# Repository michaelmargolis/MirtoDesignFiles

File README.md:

# MirtoDesignFiles

Design files for Mirto Robots

Mirto_Hubee robot has a Teensy3 controller driving HUBee wheels 

Mirto_Hotec has a teensy3 controller driving Hotec motors

Mirto_MyRio uses National Instruments myRIO to control Hotec Motors.

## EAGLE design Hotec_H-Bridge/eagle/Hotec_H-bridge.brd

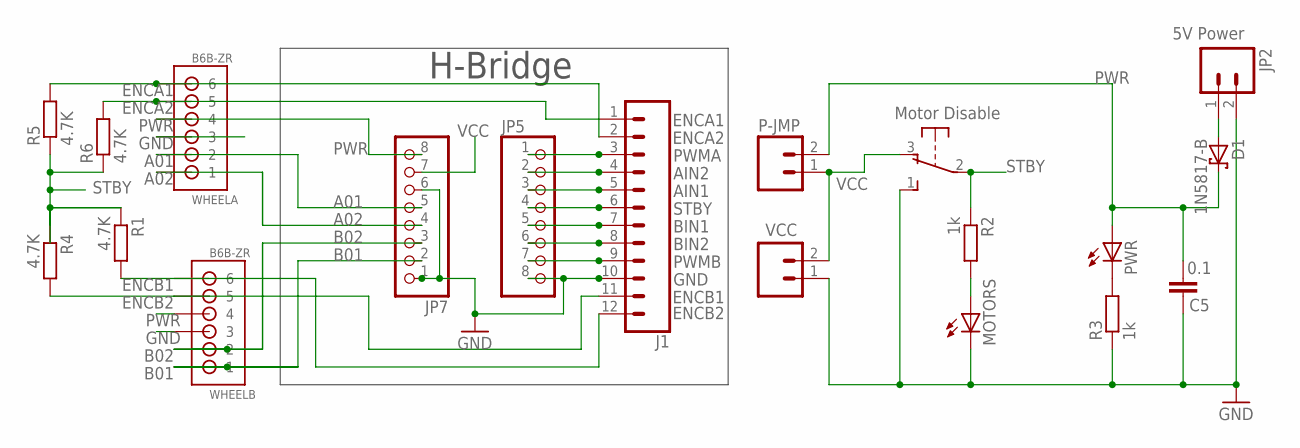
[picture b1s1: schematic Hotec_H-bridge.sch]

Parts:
C5: 0.1; CAP-PTH-SMALLEZ
D1: 1N5817-B; DO41-7.6
J1: CONN_12; 1X12
JP2: M023.5MM; SCREWTERMINAL-3.5MM-2
JP5, JP7: PINHD-1X8CLEANBIG; 1X08-CLEANBIG
MOTORS: LED3MM
P-JMP: M02PTH; 1X02
PWR: LED3MM
R1, R4, R5, R6: 4.7K; 0204/7
R2, R3: 1k; 0204/7
SW1: OS102011MA1Q
VCC: M02PTH; 1X02
WHEELA: B6B-ZR
WHEELB: B6B-ZR

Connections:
A01: JP7.5, WHEELA.2
A02: JP7.4, WHEELA.1
AIN1: J1.5, JP5.3
AIN2: J1.4, JP5.2
B01: JP7.2, WHEELB.1
B02: JP7.3, WHEELB.2
BIN1: J1.7, JP5.5
BIN2: J1.8, JP5.6
ENCA1: J1.2, R5.2, WHEELA.6
ENCA2: J1.1, R6.2, WHEELA.5
ENCB1: J1.12, R1.2, WHEELB.6
ENCB2: J1.11, R4.2, WHEELB.5
GND: C5.1, J1.10, JP2.2, JP5.8, JP7.1, JP7.6, MOTORS.K (C), R3.1, SW1.1 (S), VCC.1, WHEELA.3, WHEELB.3
unnamed: PWR.K (C), R3.2
unnamed: MOTORS.A, R2.2
unnamed: D1.A, JP2.1
PWMA: J1.3, JP5.1
PWMB: J1.9, JP5.7
PWR: C5.2, D1.C, JP7.8, P-JMP.2, PWR.A, WHEELA.4, WHEELB.4
STBY: J1.6, JP5.4, R1.1, R2.1, R4.1, R5.1, R6.1, SW1.2
VCC: JP7.7, P-JMP.1, SW1.3 (O), VCC.2

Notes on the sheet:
Motor Disable
5V Power
H-Bridge

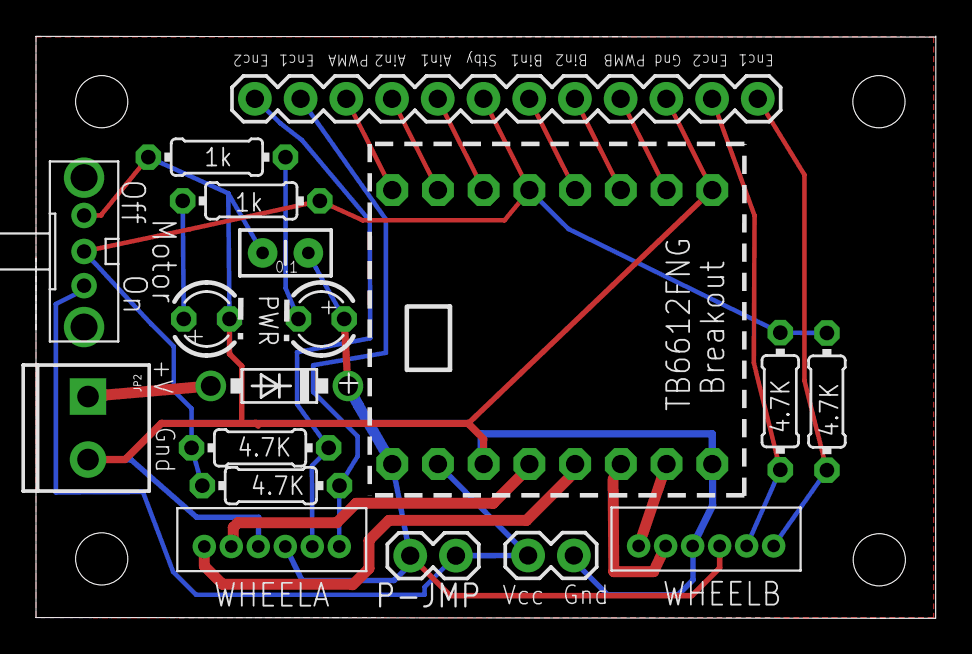
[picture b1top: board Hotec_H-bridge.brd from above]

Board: 2 copper layers, 50.0 x 32.4 mm, 19 parts (0 on the bottom side), 21 nets.

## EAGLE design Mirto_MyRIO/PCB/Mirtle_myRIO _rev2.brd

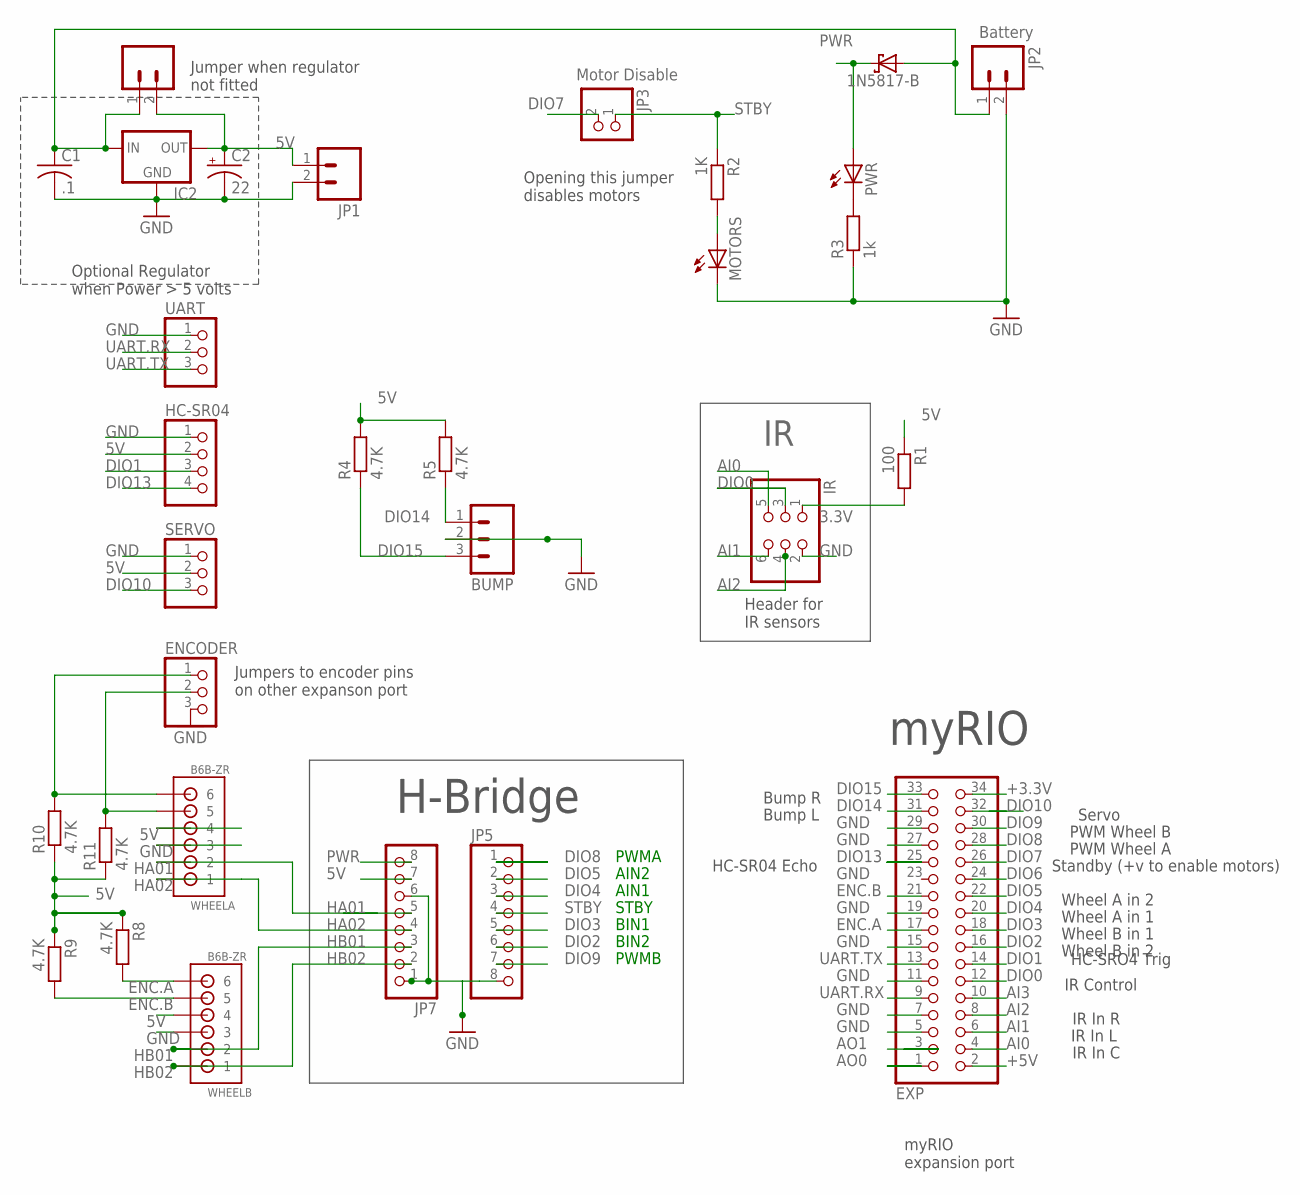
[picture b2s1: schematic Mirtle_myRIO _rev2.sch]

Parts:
5VJMPR: M02PTH; 1X02
BUMP: M03SCREW; SCREWTERMINAL-3.5MM-3
C1: .1; C025-024X044
C2: 22; E2-5
D1: 1N5817-B; DO41-7.6
ENCODER: PINHD-1X3/90; 1X03/90
EXP: PINHD-2X17/90; 2X17/90
HC-SR04: PINHD-1X4/90; 1X04/90
IC2: 78MXXS
IR: PINHD-2X3; 2X03
JP1, JP2: M023.5MM; SCREWTERMINAL-3.5MM-2
JP3: PINHD-1X2/90; 1X02/90
JP5, JP7: PINHD-1X8CLEANBIG; 1X08-CLEANBIG
MOTORS: LED3MM
PWR: LED3MM
R1: 100; 0204/7
R2: 1K; 0204/7
R3: 1k; 0204/7
R4, R5, R8, R9, R10, R11: 4.7K; 0204/7
SERVO: PINHD-1X3/90; 1X03/90
UART: PINHD-1X3/90; 1X03/90
WHEELA: B6B-ZR
WHEELB: B6B-ZR

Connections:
3.3V: IR.1, R1.2
5V: 5VJMPR.2, C2.+, HC-SR04.2, IC2.OUT, JP1.1, JP7.7, R1.1, R4.2, R5.2, R8.1, R9.1, R10.1, R11.1, SERVO.2, WHEELA.4, WHEELB.4
+3.3V: EXP.34
+5V: EXP.2
AI0: EXP.4, IR.5
AI1: EXP.6, IR.6
AI2: EXP.8, IR.4
AI3: EXP.10
AO0: EXP.1
AO1: EXP.3
BAT+V: 5VJMPR.1, C1.1, D1.A, IC2.IN, JP2.1
D31: ENCODER.1, R10.2, WHEELA.6
DIO0: EXP.12, IR.3
DIO1: EXP.14, HC-SR04.3
DIO2: EXP.16, JP5.6
DIO3: EXP.18, JP5.5
DIO4: EXP.20, JP5.3
DIO5: EXP.22, JP5.2
DIO6: EXP.24
DIO7: EXP.26, JP3.2
DIO8: EXP.28, JP5.1
DIO9: EXP.30, JP5.7
DIO10: EXP.32, SERVO.3
DIO13: EXP.25, HC-SR04.4
DIO14: BUMP.1, EXP.31, R5.1
DIO15: BUMP.3, EXP.33, R4.1
ENC.A: EXP.17, R8.2, WHEELB.6
ENC.B: EXP.21, R9.2, WHEELB.5
GND: BUMP.2, C1.2, C2.-, ENCODER.3, EXP.5, EXP.7, EXP.11, EXP.15, EXP.19, EXP.27, EXP.29, HC-SR04.1, IC2.GND, IR.2, JP1.2, JP2.2, JP5.8, JP7.1, JP7.6, MOTORS.K (C), R3.1, SERVO.1, UART.1, WHEELA.3, WHEELB.3
HA01: JP7.5, WHEELA.2
HA02: JP7.4, WHEELA.1
HB01: JP7.3, WHEELB.2
HB02: JP7.2, WHEELB.1
unnamed: PWR.K (C), R3.2
unnamed: ENCODER.2, R11.2, WHEELA.5
unnamed: MOTORS.A, R2.2
PWR: D1.C, JP7.8, PWR.A
STBY: JP3.1, JP5.4, R2.1
UART.RX: EXP.9, UART.2
UART.TX: EXP.13, UART.3

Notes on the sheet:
Motor Disable
Battery
Header for IR sensors
H-Bridge
myRIO
Jumpers to encoder pins on other expanson port
STBY
myRIO expansion port
AIN1
AIN2
PWMA
BIN1
BIN2
PWMB
IR In L
IR Control
Bump L
IR In C
IR In R
Bump R
HC-SR04 Echo
PWM Wheel A
PWM Wheel B
Wheel B in 1
Wheel B in 2
Wheel A in 1
Wheel A in 2
Servo
HC-SRO4 Trig
Standby (+v to enable motors)
Optional Regulator when Power > 5 volts
Jumper when regulator not fitted
Opening this jumper disables motors

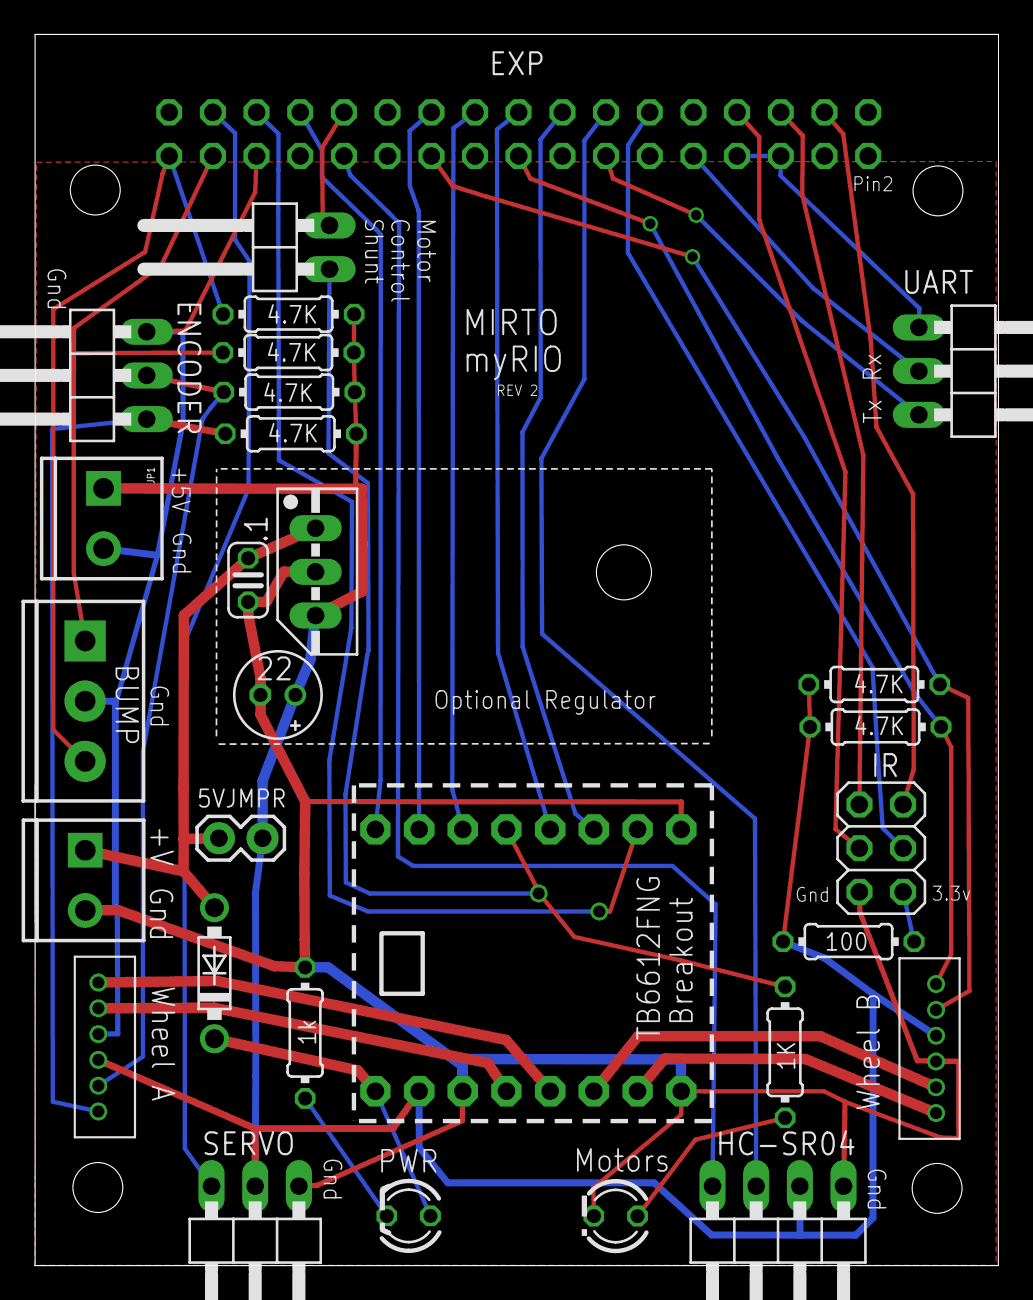
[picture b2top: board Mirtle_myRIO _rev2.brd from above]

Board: 4 copper layers, 56.1 x 71.6 mm, 30 parts (1 on the bottom side), 34 nets.

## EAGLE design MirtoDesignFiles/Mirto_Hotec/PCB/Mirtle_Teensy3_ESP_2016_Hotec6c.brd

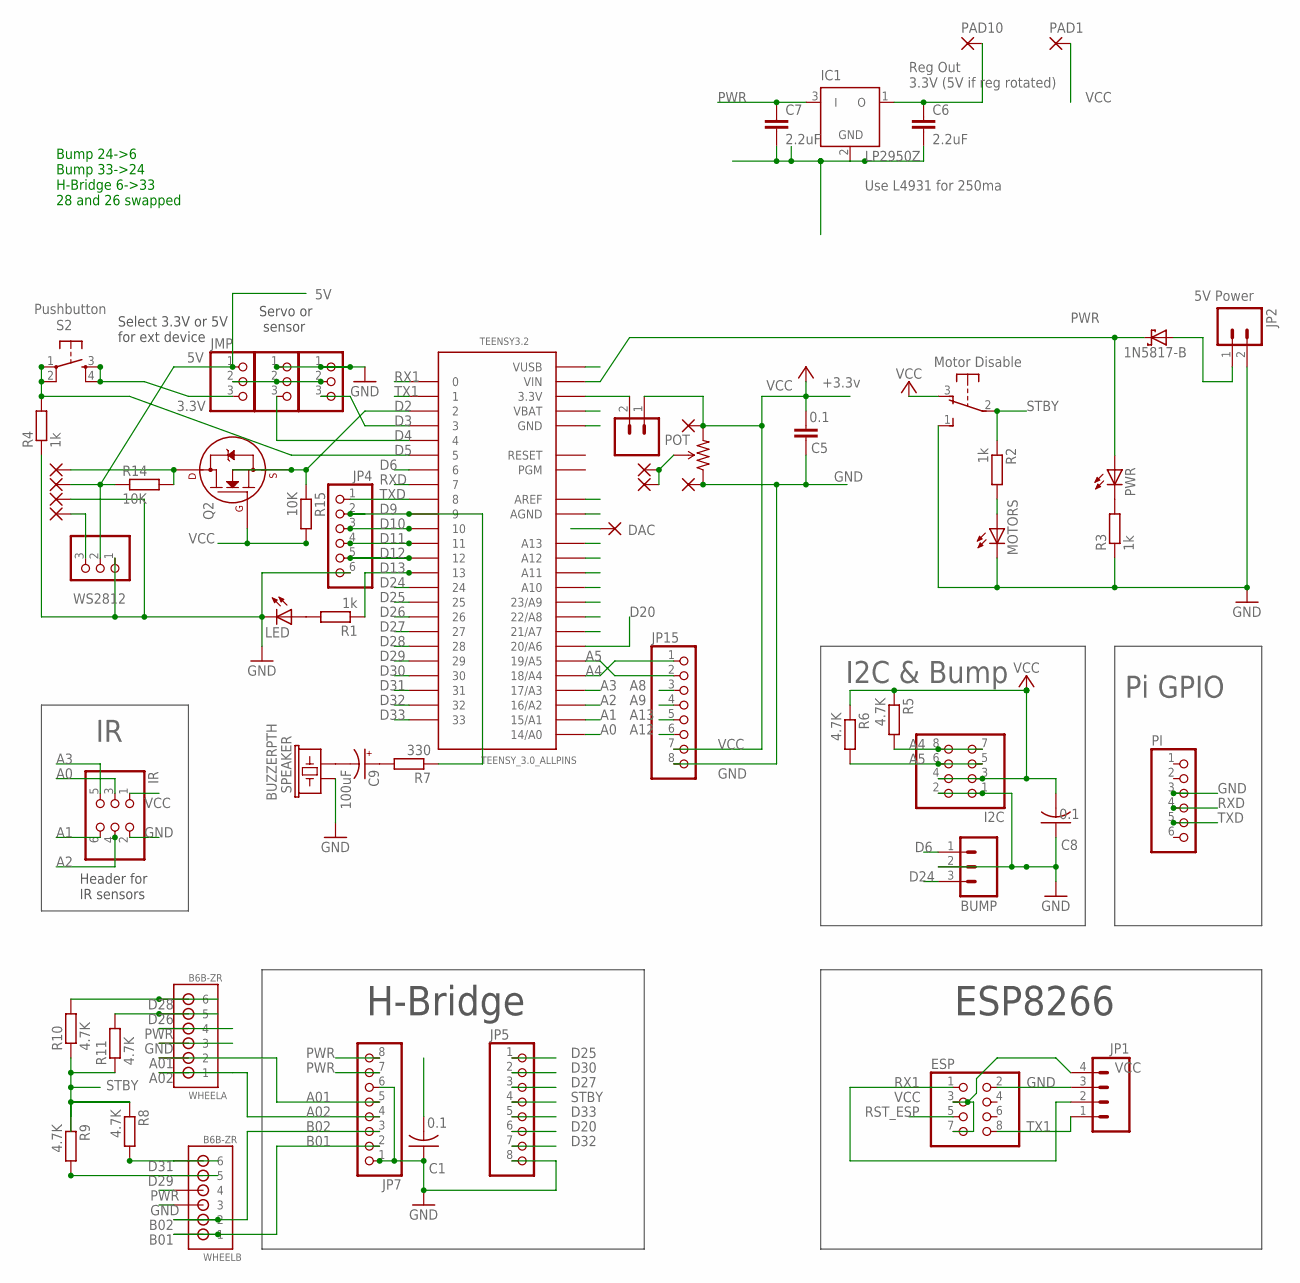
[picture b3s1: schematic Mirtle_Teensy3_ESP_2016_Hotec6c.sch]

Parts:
3V3: M02PTH; 1X02
BUMP: M03SCREW; SCREWTERMINAL-3.5MM-3
C1, C8: 0.1; C025-024X044
C5: 0.1; CAP-PTH-SMALLEZ
C6, C7: 2.2uF; C050-024X044
C9: 100uF; E2,5-5
D1: 1N5817-B; DO41-7.6
DAC: 1,6/0,8
ESP: PINHD-2X4; 2X04
EXT, EXT1: PINHD-1X3; 1X03
I2C: PINHD-2X4; 2X04
IC1: LP2950Z; TO92
IR: PINHD-2X3; 2X03
JMP: PINHD-1X3; 1X03
JP1: M04PTH; 1X04
JP2: M023.5MM; SCREWTERMINAL-3.5MM-2
JP4: PINHD-1X6B; 1X06-BIG
JP5, JP7: PINHD-1X8CLEANBIG; 1X08-CLEANBIG
JP15: PINHD-1X8BIG; 1X08-BIG
LED: LED3MM
MOTORS: LED3MM
PAD1, PAD2, PAD3, PAD4, PAD5, PAD6, PAD7, PAD8, PAD9, PAD10: 1,6/0,8
PI: PINHD-1X6; 1X06
POT: TSR-3386; 3386U
PWR: LED3MM
Q2: 2N7000_TO92; TO-92
R1, R2, R3, R4: 1k; 0204/7
R5, R6: 4.7K; 0204/7
R7: 330; 0204/7
R8, R9, R10, R11: 4.7K; 0204/5
R14, R15: 10K; 0204/5
S2: TAC_SWITCHPTH; TACTILE-PTH
SPEAKER: BUZZERPTH; BUZZER-12MM
SW1: OS102011MA1Q
TEENSY3.2: TEENSY_3.0_ALLPINS
WHEELA: B6B-ZR
WHEELB: B6B-ZR
WS2812: PINHD-1X3; 1X03

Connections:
2N700: PAD2.1, Q2.3 (D), R14.2
5VIN: C1.2, D1.A, JP2.1
A0: IR.3, TEENSY3.2.14/A0
A1: IR.6, TEENSY3.2.15/A1
A01: JP7.5, WHEELA.2
A2: IR.4, TEENSY3.2.16/A2
A02: JP7.4, WHEELA.1
A3: IR.5, TEENSY3.2.17/A3
A4: I2C.7, I2C.8, JP15.1, R5.2, TEENSY3.2.18/A4
A5: I2C.5, I2C.6, JP15.2, R6.2, TEENSY3.2.19/A5
A7: PAD6.1, PAD9.1, POT.2 (WIPER), TEENSY3.2.21/A7
A8: JP15.3, TEENSY3.2.22/A8
A9: JP15.4, TEENSY3.2.23/A9
A10: TEENSY3.2.A10
A11: TEENSY3.2.A11
A12: JP15.6, TEENSY3.2.A12
A13: JP15.5, TEENSY3.2.A13
B01: JP7.2, WHEELB.1
B02: JP7.3, WHEELB.2
D2: Q2.1 (S), R15.1, TEENSY3.2.2
D3: EXT.3, TEENSY3.2.3
D4: EXT1.3, TEENSY3.2.4
D5: R4.2, S2.1, S2.2, TEENSY3.2.5
D6: BUMP.1, TEENSY3.2.6
D9: JP4.2, R7.1, TEENSY3.2.9
D10: JP4.3, TEENSY3.2.10
D11: JP4.4, TEENSY3.2.11
D12: JP4.5, TEENSY3.2.12
D13: R1.1, TEENSY3.2.13
D20: JP5.6, TEENSY3.2.20/A6
D24: BUMP.3, TEENSY3.2.24
D25: JP5.1, TEENSY3.2.25
D26: R11.2, TEENSY3.2.26, WHEELA.5
D27: JP5.3, TEENSY3.2.27
D28: R10.2, TEENSY3.2.28, WHEELA.6
D29: R9.2, TEENSY3.2.29, WHEELB.5
D30: JP5.2, TEENSY3.2.30
D31: R8.2, TEENSY3.2.31, WHEELB.6
D32: JP5.7, TEENSY3.2.32
D33: JP5.5, TEENSY3.2.33
GND: BUMP.2, C1.1, C5.1, C6.2, C7.2, C8.1, ESP.2, EXT.1, EXT1.1, I2C.1, I2C.2, IC1.2 (GND), IR.2, JP1.3, JP2.2, JP4.6, JP5.8, JP7.1, JP7.6, JP15.8, LED.K (C), MOTORS.K (C), PAD4.1, PAD8.1, PI.3, POT.1 (CCW), R3.1, R4.1, SPEAKER.+ (1), SW1.1 (S), TEENSY3.2.AGND, TEENSY3.2.GND, TEENSY3.2.GND1 (GND), TEENSY3.2.GND2 (GND), WHEELA.3, WHEELB.3, WS2812.1
unnamed: PWR.K (C), R3.2
unnamed: LED.A, R1.2
unnamed: 3V3.2, TEENSY3.2.3.3V, TEENSY3.2.3.3V1 (3.3V), TEENSY3.2.3.3V2 (3.3V)
unnamed: MOTORS.A, R2.2
unnamed: C6.1, IC1.1 (O), PAD10.1
unnamed: PAD5.1, WS2812.3
unnamed: EXT.2, EXT1.2, JMP.2
unnamed: C9.-, SPEAKER.- (2)
unnamed: C9.+, R7.2
PWR: C7.1, D1.C, IC1.3 (I), JMP.1, JP7.7, JP7.8, PAD3.1, PWR.A, R14.1, TEENSY3.2.VIN, WHEELA.4, WHEELB.4, WS2812.2
RST_ESP: ESP.5
RX1: ESP.1, JP1.2, TEENSY3.2.0
RXD: PI.4, TEENSY3.2.7
STBY: JP5.4, R2.1, R8.1, R9.1, R10.1, R11.1, SW1.2
TX1: ESP.8, JP1.1, TEENSY3.2.1
TXD: JP4.1, PI.5, TEENSY3.2.8
VCC: 3V3.1, C5.2, C8.2, ESP.3, ESP.7, I2C.3, I2C.4, IR.1, JMP.3, JP1.4, JP15.7, PAD1.1, PAD7.1, POT.3 (CW), Q2.2 (G), R5.1, R6.1, R15.2, S2.3, S2.4, SW1.3 (O)

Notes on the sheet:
Motor Disable
5V Power
+3.3v
3.3V
Servo or sensor
Select 3.3V or 5V for ext device
Header for IR sensors
Pushbutton
H-Bridge
ESP8266
Pi GPIO
I2C & Bump
Reg Out 3.3V (5V if reg rotated)
Use L4931 for 250ma
Bump 24->6 Bump 33->24 H-Bridge 6->33 28 and 26 swapped

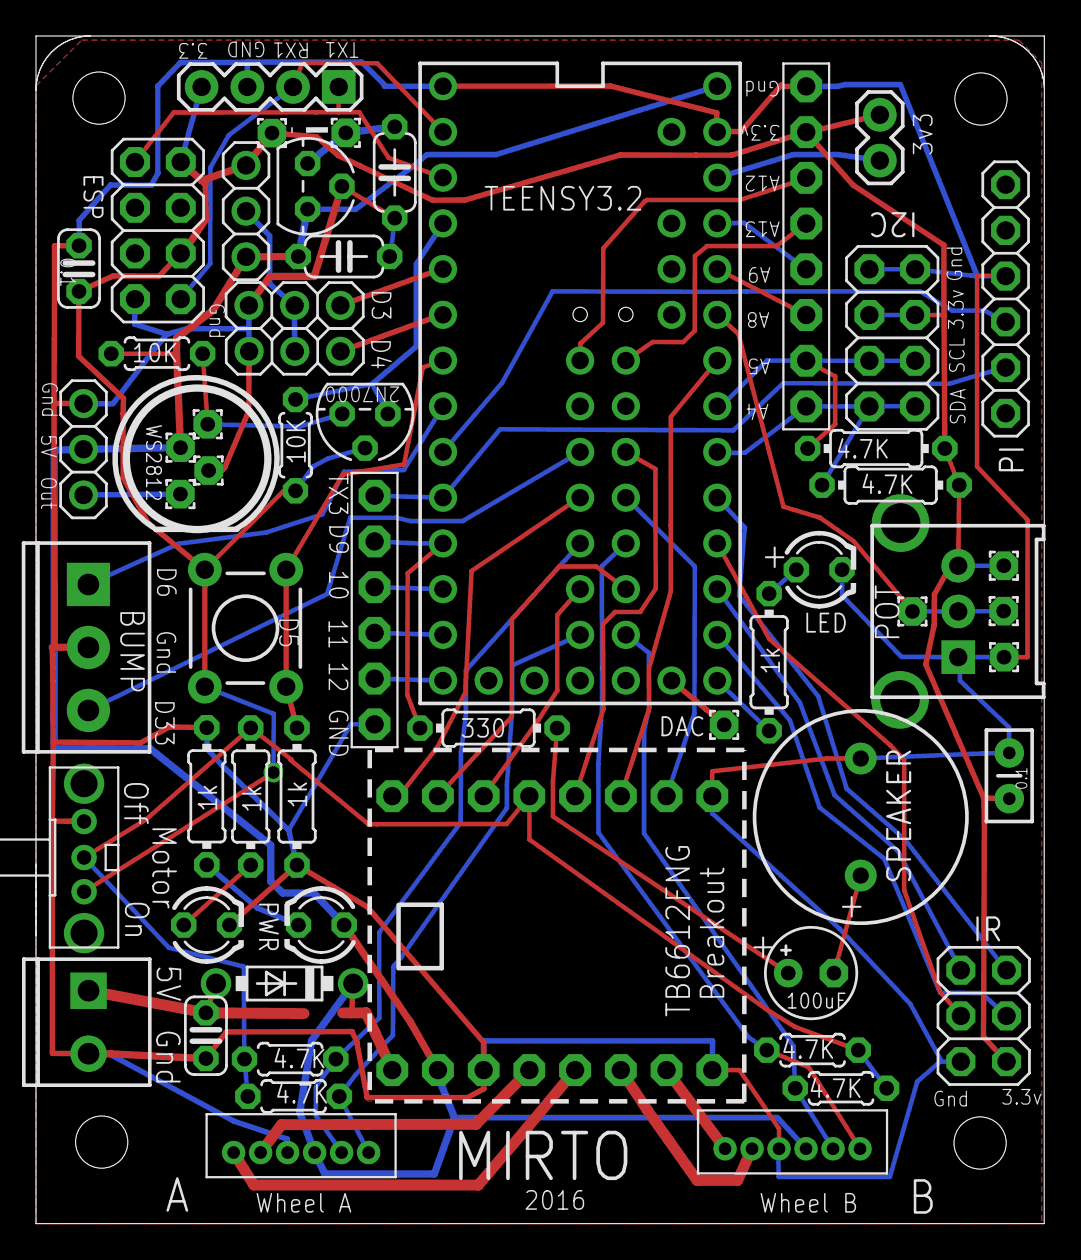
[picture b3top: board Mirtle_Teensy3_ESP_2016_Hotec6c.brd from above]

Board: 2 copper layers, 56.0 x 66.0 mm, 59 parts (0 on the bottom side), 55 nets.

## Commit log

2017-03-19 Added Readme file
2017-03-19 updated directories
2017-03-19 Added motor specs to build document
2017-03-19 removed old build doc
2017-03-20 Added info on H-bridge stand-alone board
2018-03-19 Commit build doc
2018-03-24 Initial commit of Arduino test sketch for Mirto 2016 PCB

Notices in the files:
parts and their libraries:
SparkFun-Passives: Licensing: CC v3.0 Share-Alike You are welcome to use this library for commercial purposes.
